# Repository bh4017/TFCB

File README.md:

# TFCB

# DESCRIPTION

A PIC 18F87J50 platform consisting of a baseboard which provides a means to easily design interface 'hats' for adding functionality.  

The baseboard includes all the basic components necessary to run an 18F87J50 Microcontroller, plus some communications ports (USB, RS232, SPI) and on-board power supplies.

The baseboard breaks out the 18F87J50 pins to 2.54mm IO which allows hats to be easily created by professional and amateur electronics users.  It is possible to build hats from stripboard or custom PCBs.  The 18F87J50 is extremely well equipped and even includes on-chip USB2.0, so USB based PIC projects can be created and prototyped very easily.

Some hats created by the author for various applications will be included under the /hats directory.

# LICENSE

This documentation describes Open Hardware and is licensed under the CERN Open Hardware Licence v1.2. You may redistribute and modify this documentation under the terms of the CERN OHL v1.2 (http://ohwr.org/cernohl). This documentation is distributed WITHOUT ANY EXPRESS OR IMPLIED WARRANTY, INCLUDING OF MERCHANTABILITY, SATISFACTORY QUALITY AND FITNESS FOR A PARTICULAR PURPOSE.  Please see the CERN OHL v1.2 for applicable conditions.

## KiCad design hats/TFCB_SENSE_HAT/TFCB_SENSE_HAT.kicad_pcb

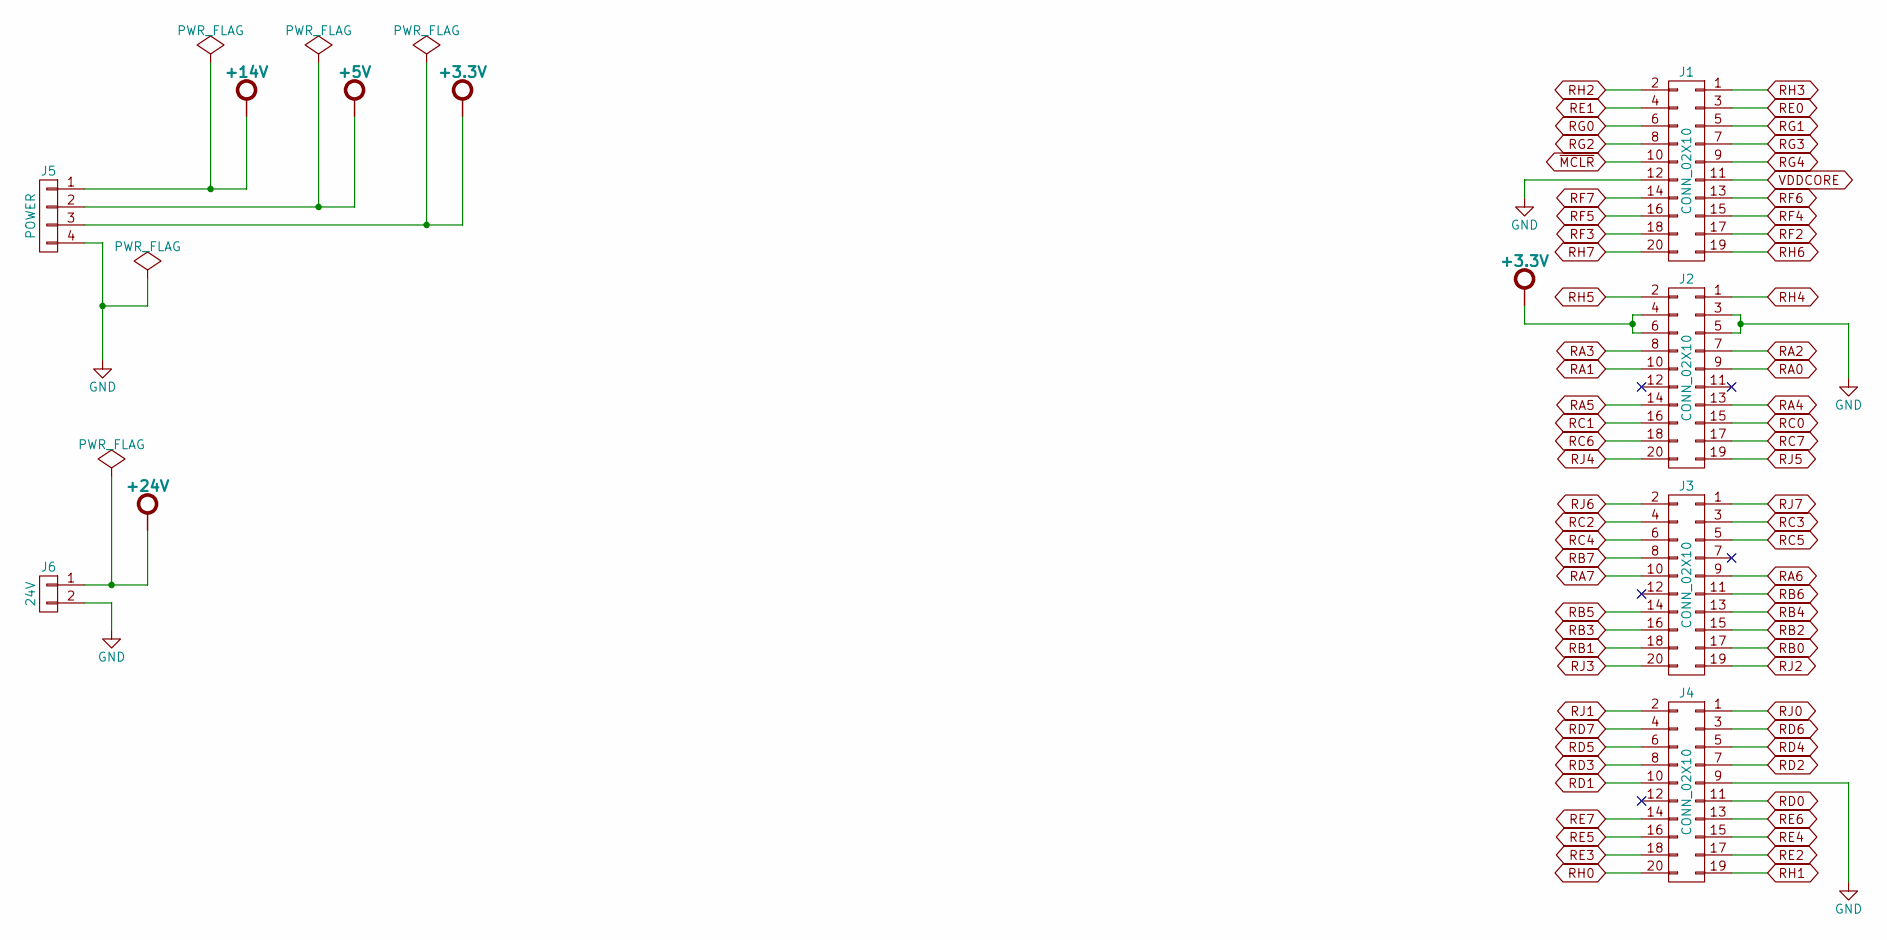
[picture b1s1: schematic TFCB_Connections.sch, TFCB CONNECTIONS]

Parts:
J1, J2, J3, J4: CONN_02X10; RCPT-2row-2.54mm-20way
J5: POWER; Weidmuller-SL-5.08-Vertical-4Pole
J6: 24V; Weidmuller-SL-5.08-Vertical-2Pole

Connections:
+3.3V: J2.4, J2.6, J5.3
+5V: J5.2
+14V: J5.1
+24V: J6.1
GND: J1.12, J2.3, J2.5, J4.9, J5.4, J6.2
RA0: J2.9
RA1: J2.10
RA2: J2.7
RA3: J2.8
RA4: J2.13
RA5: J2.14
RA6: J3.9
RA7: J3.10
RB0: J3.17
RB1: J3.18
RB2: J3.15
RB3: J3.16
RB4: J3.13
RB5: J3.14
RB6: J3.11
RB7: J3.8
RC0: J2.15
RC1: J2.16
RC2: J3.4
RC3: J3.3
RC4: J3.6
RC5: J3.5
RC6: J2.18
RC7: J2.17
RD0: J4.11
RD1: J4.10
RD2: J4.7
RD3: J4.8
RD4: J4.5
RD5: J4.6
RD6: J4.3
RD7: J4.4
RE0: J1.3
RE1: J1.4
RE2: J4.17
RE3: J4.18
RE4: J4.15
RE5: J4.16
RE6: J4.13
RE7: J4.14
RF2: J1.17
RF3: J1.18
RF4: J1.15
RF5: J1.16
RF6: J1.13
RF7: J1.14
RG0: J1.6
RG1: J1.5
RG2: J1.8
RG3: J1.7
RG4: J1.9
RH0: J4.20
RH1: J4.19
RH2: J1.2
RH3: J1.1
RH4: J2.1
RH5: J2.2
RH6: J1.19
RH7: J1.20
RJ0: J4.1
RJ1: J4.2
RJ2: J3.19
RJ3: J3.20
RJ4: J2.20
RJ5: J2.19
RJ6: J3.2
RJ7: J3.1
VDDCORE: J1.11
~MCLR: J1.10

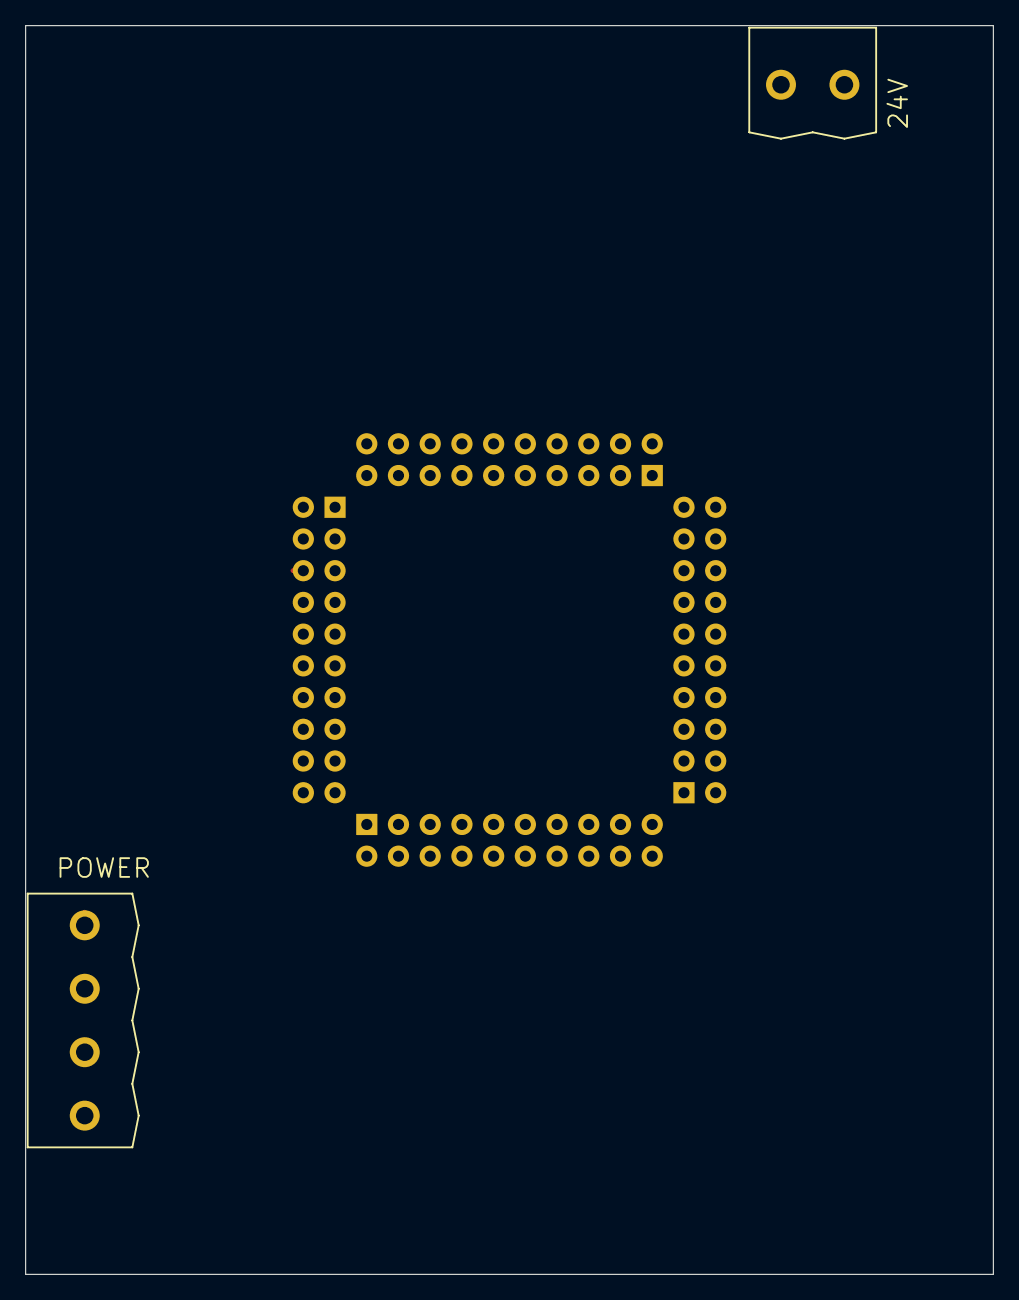
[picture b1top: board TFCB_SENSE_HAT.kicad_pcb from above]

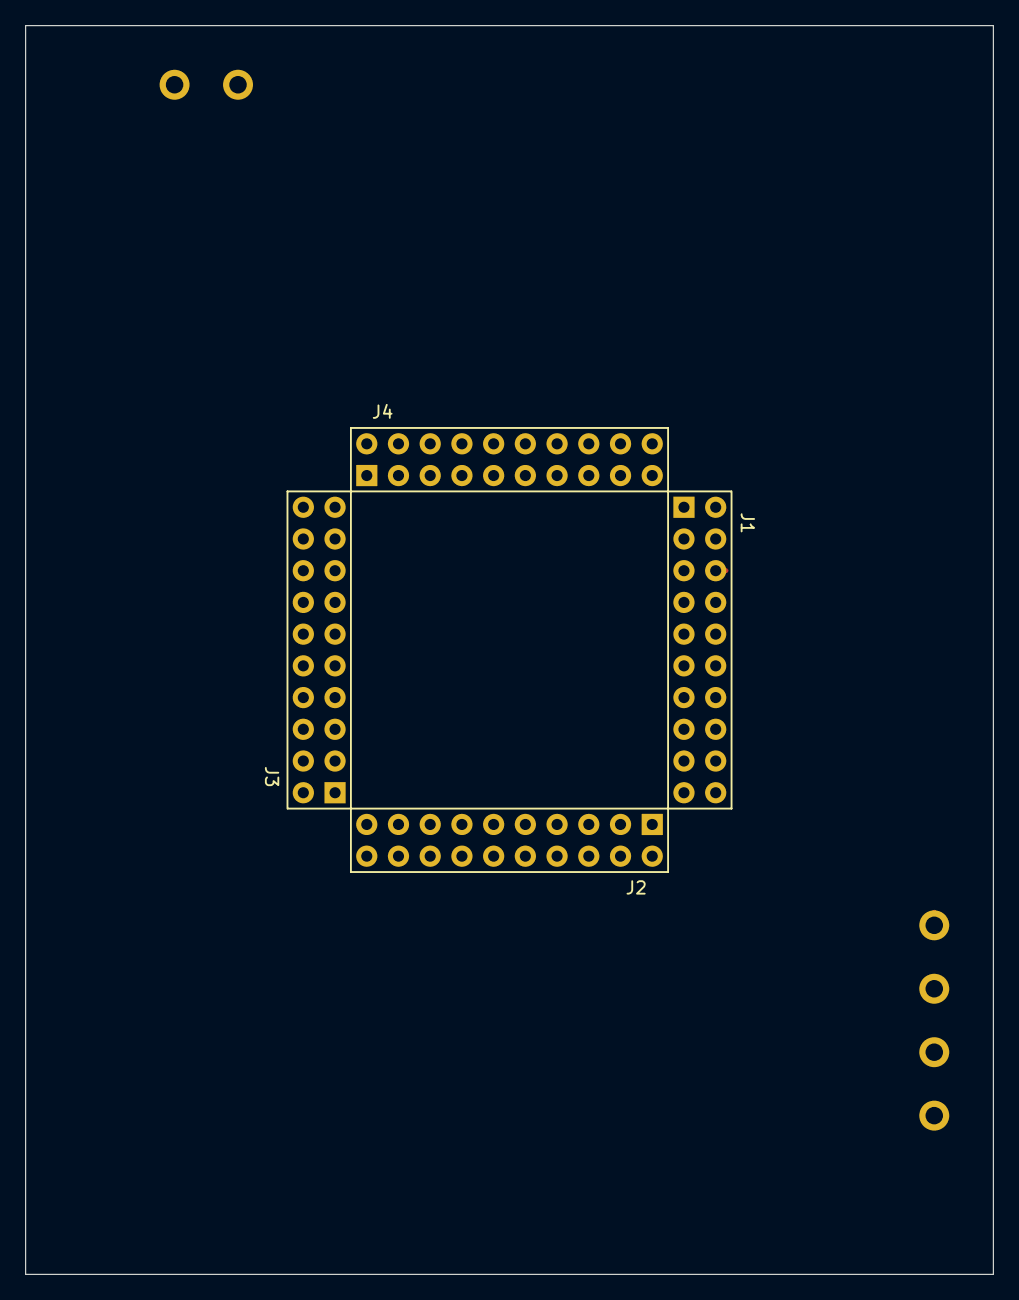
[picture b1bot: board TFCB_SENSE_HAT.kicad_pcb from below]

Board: 2 copper layers, 77.5 x 100.0 mm, 6 parts (4 on the bottom side), 2 nets.

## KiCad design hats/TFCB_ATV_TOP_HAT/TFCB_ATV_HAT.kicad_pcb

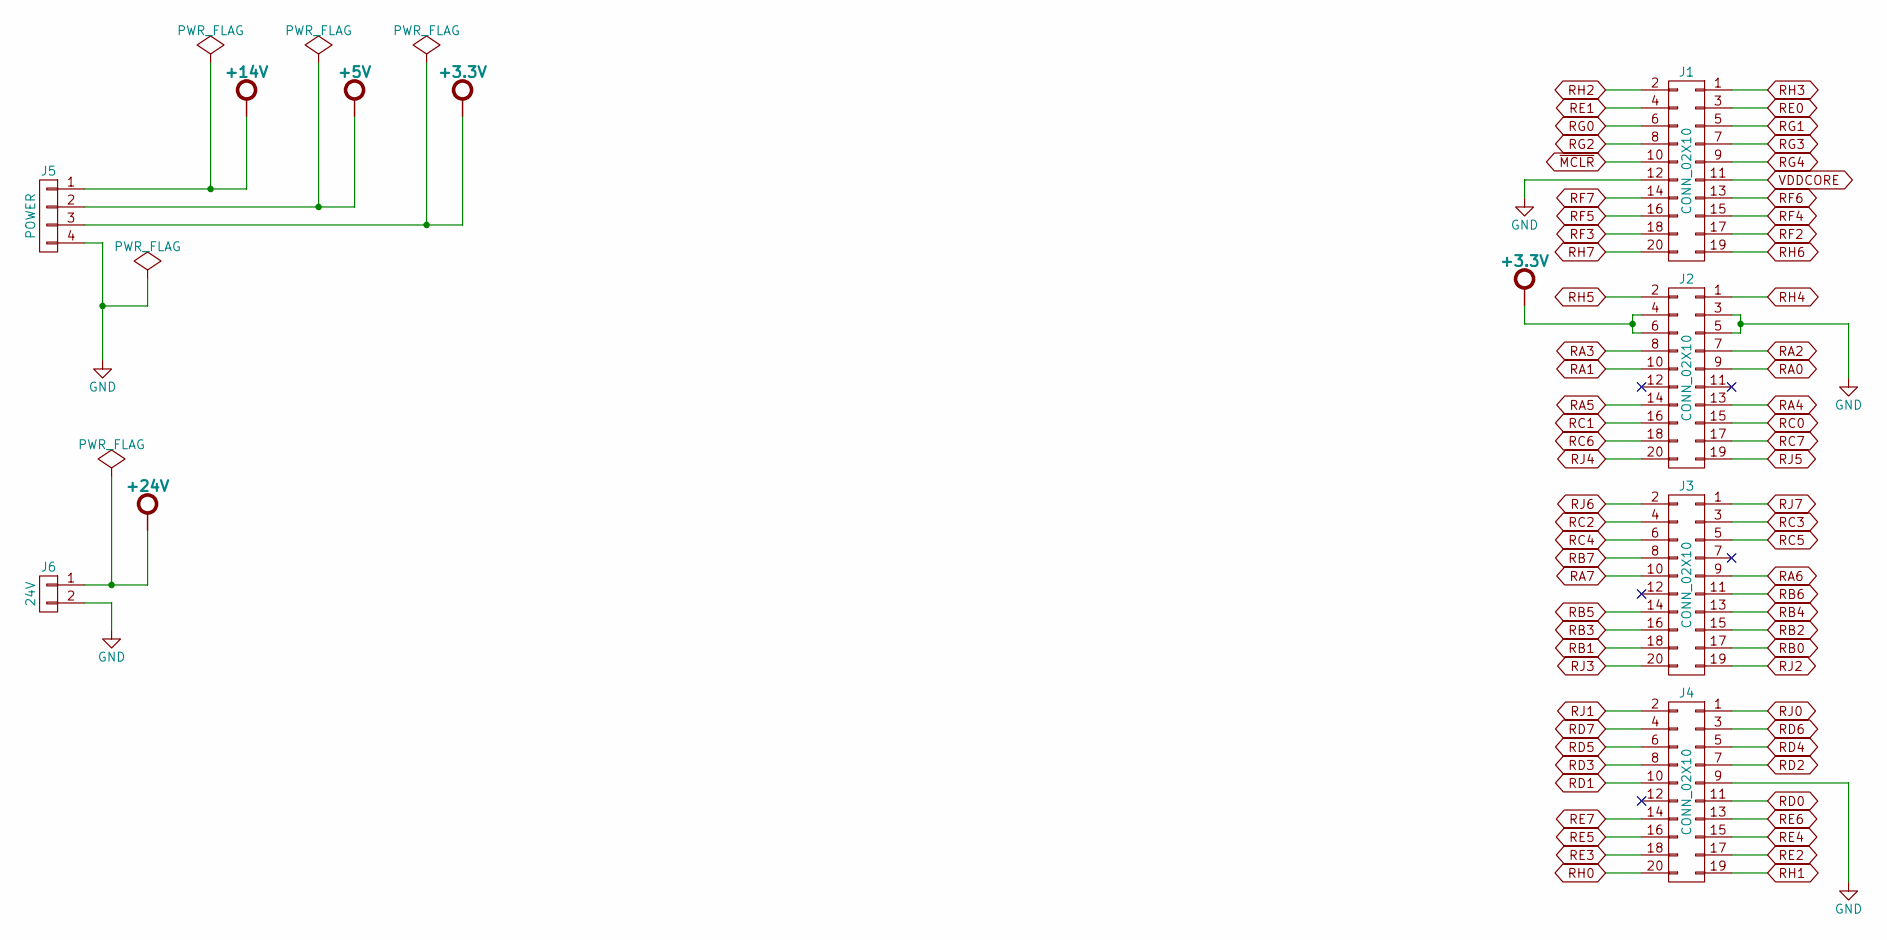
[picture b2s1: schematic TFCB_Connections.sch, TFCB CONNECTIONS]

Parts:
J1, J2, J3, J4: CONN_02X10; RCPT-2row-2.54mm-20way
J5: POWER; Weidmuller-SL-5.08-Vertical-4Pole
J6: 24V; Weidmuller-SL-5.08-Vertical-2Pole

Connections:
+3.3V: J2.4, J2.6, J5.3; also elsewhere on the board
+5V: J5.2; also elsewhere on the board
+14V: J5.1; also elsewhere on the board
+24V: J6.1; also elsewhere on the board
GND: J1.12, J2.3, J2.5, J4.9, J5.4, J6.2; also elsewhere on the board
RA0: J2.9; also elsewhere on the board
RA1: J2.10; also elsewhere on the board
RA2: J2.7
RA3: J2.8
RA4: J2.13; also elsewhere on the board
RA5: J2.14
RA6: J3.9
RA7: J3.10
RB0: J3.17
RB1: J3.18
RB2: J3.15
RB3: J3.16
RB4: J3.13
RB5: J3.14
RB6: J3.11
RB7: J3.8
RC0: J2.15
RC1: J2.16
RC2: J3.4; also elsewhere on the board
RC3: J3.3
RC4: J3.6
RC5: J3.5
RC6: J2.18
RC7: J2.17
RD0: J4.11
RD1: J4.10
RD2: J4.7
RD3: J4.8
RD4: J4.5
RD5: J4.6
RD6: J4.3
RD7: J4.4
RE0: J1.3
RE1: J1.4
RE2: J4.17
RE3: J4.18
RE4: J4.15
RE5: J4.16
RE6: J4.13; also elsewhere on the board
RE7: J4.14; also elsewhere on the board
RF2: J1.17; also elsewhere on the board
RF3: J1.18
RF4: J1.15
RF5: J1.16
RF6: J1.13
RF7: J1.14
RG0: J1.6; also elsewhere on the board
RG1: J1.5
RG2: J1.8
RG3: J1.7; also elsewhere on the board
RG4: J1.9; also elsewhere on the board
RH0: J4.20; also elsewhere on the board
RH1: J4.19
RH2: J1.2
RH3: J1.1
RH4: J2.1; also elsewhere on the board
RH5: J2.2; also elsewhere on the board
RJ0: J4.1
RJ1: J4.2
RJ2: J3.19
RJ3: J3.20; also elsewhere on the board
RJ4: J2.20
RJ5: J2.19
RJ6: J3.2; also elsewhere on the board
RJ7: J3.1; also elsewhere on the board
VDDCORE: J1.11
~MCLR: J1.10

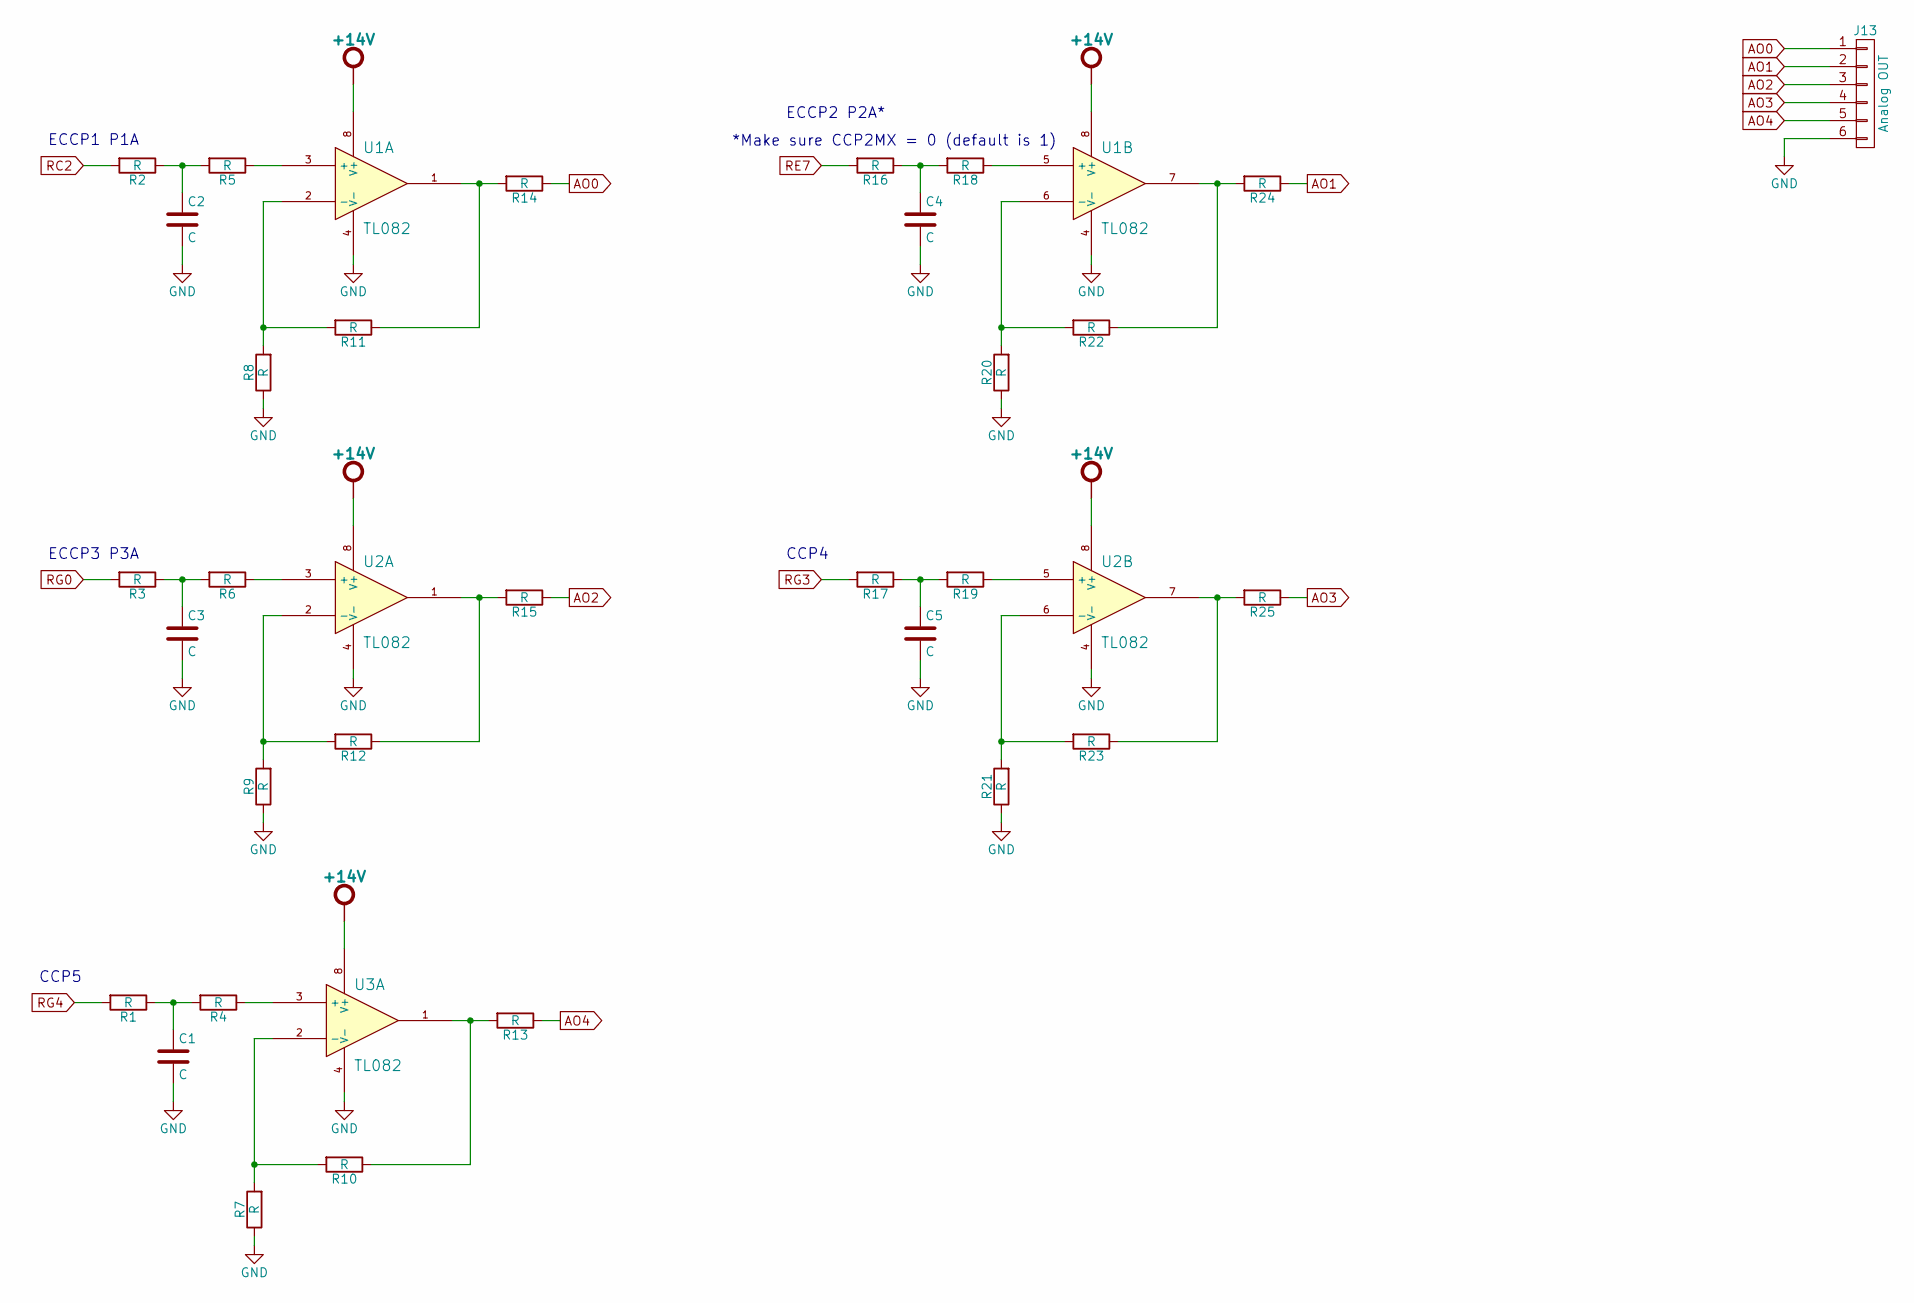
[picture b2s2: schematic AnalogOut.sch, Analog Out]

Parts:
C1, C2, C3, C4, C5: C; C_0805_HandSoldering
J13: Analog OUT; Weidmuller-SL-5.08-Vertical-6Pole
R1, R2, R3, R4, R5, R6, R7, R8, R9, R10, R11, R12, R13, R14, R15, R16, R17, R18, R19, R20, R21, R22, R23, R24, R25: R; R_0805_HandSoldering
U1, U2, U3: TL082; SOIC-8_3.9x4.9mm_Pitch1.27mm

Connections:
+14V: U1.8 (V+), U2.8 (V+), U3.8 (V+); also elsewhere on the board
AO0: J13.1, R14.1
AO1: J13.2, R24.1
AO2: J13.3, R15.1
AO3: J13.4, R25.1
AO4: J13.5, R13.1
GND: C1.2, C2.2, C3.2, C4.2, C5.2, J13.6, R7.1, R8.1, R9.1, R20.1, R21.1, U1.4 (V-), U2.4 (V-), U3.4 (V-); also elsewhere on the board
unnamed: C1.1, R1.1, R4.2
unnamed: C2.1, R2.1, R5.2
unnamed: C3.1, R3.1, R6.2
unnamed: C4.1, R16.1, R18.2
unnamed: C5.1, R17.1, R19.2
unnamed: R4.1, U3.3 (+)
unnamed: R5.1, U1.3 (+)
unnamed: R6.1, U2.3 (+)
unnamed: R10.1, R13.2, U3.1
unnamed: R7.2, R10.2, U3.2 (-)
unnamed: R11.1, R14.2, U1.1
unnamed: R8.2, R11.2, U1.2 (-)
unnamed: R12.1, R15.2, U2.1
unnamed: R9.2, R12.2, U2.2 (-)
unnamed: R18.1, U1.5 (+)
unnamed: R19.1, U2.5 (+)
unnamed: R20.2, R22.2, U1.6 (-)
unnamed: R21.2, R23.2, U2.6 (-)
unnamed: R22.1, R24.2, U1.7
unnamed: R23.1, R25.2, U2.7
RC2: R2.2; also elsewhere on the board
RE7: R16.2; also elsewhere on the board
RG0: R3.2; also elsewhere on the board
RG3: R17.2; also elsewhere on the board
RG4: R1.2; also elsewhere on the board

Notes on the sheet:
ECCP1 P1A
ECCP3 P3A
ECCP2 P2A*
CCP5
CCP4
*Make sure CCP2MX = 0 (default is 1)

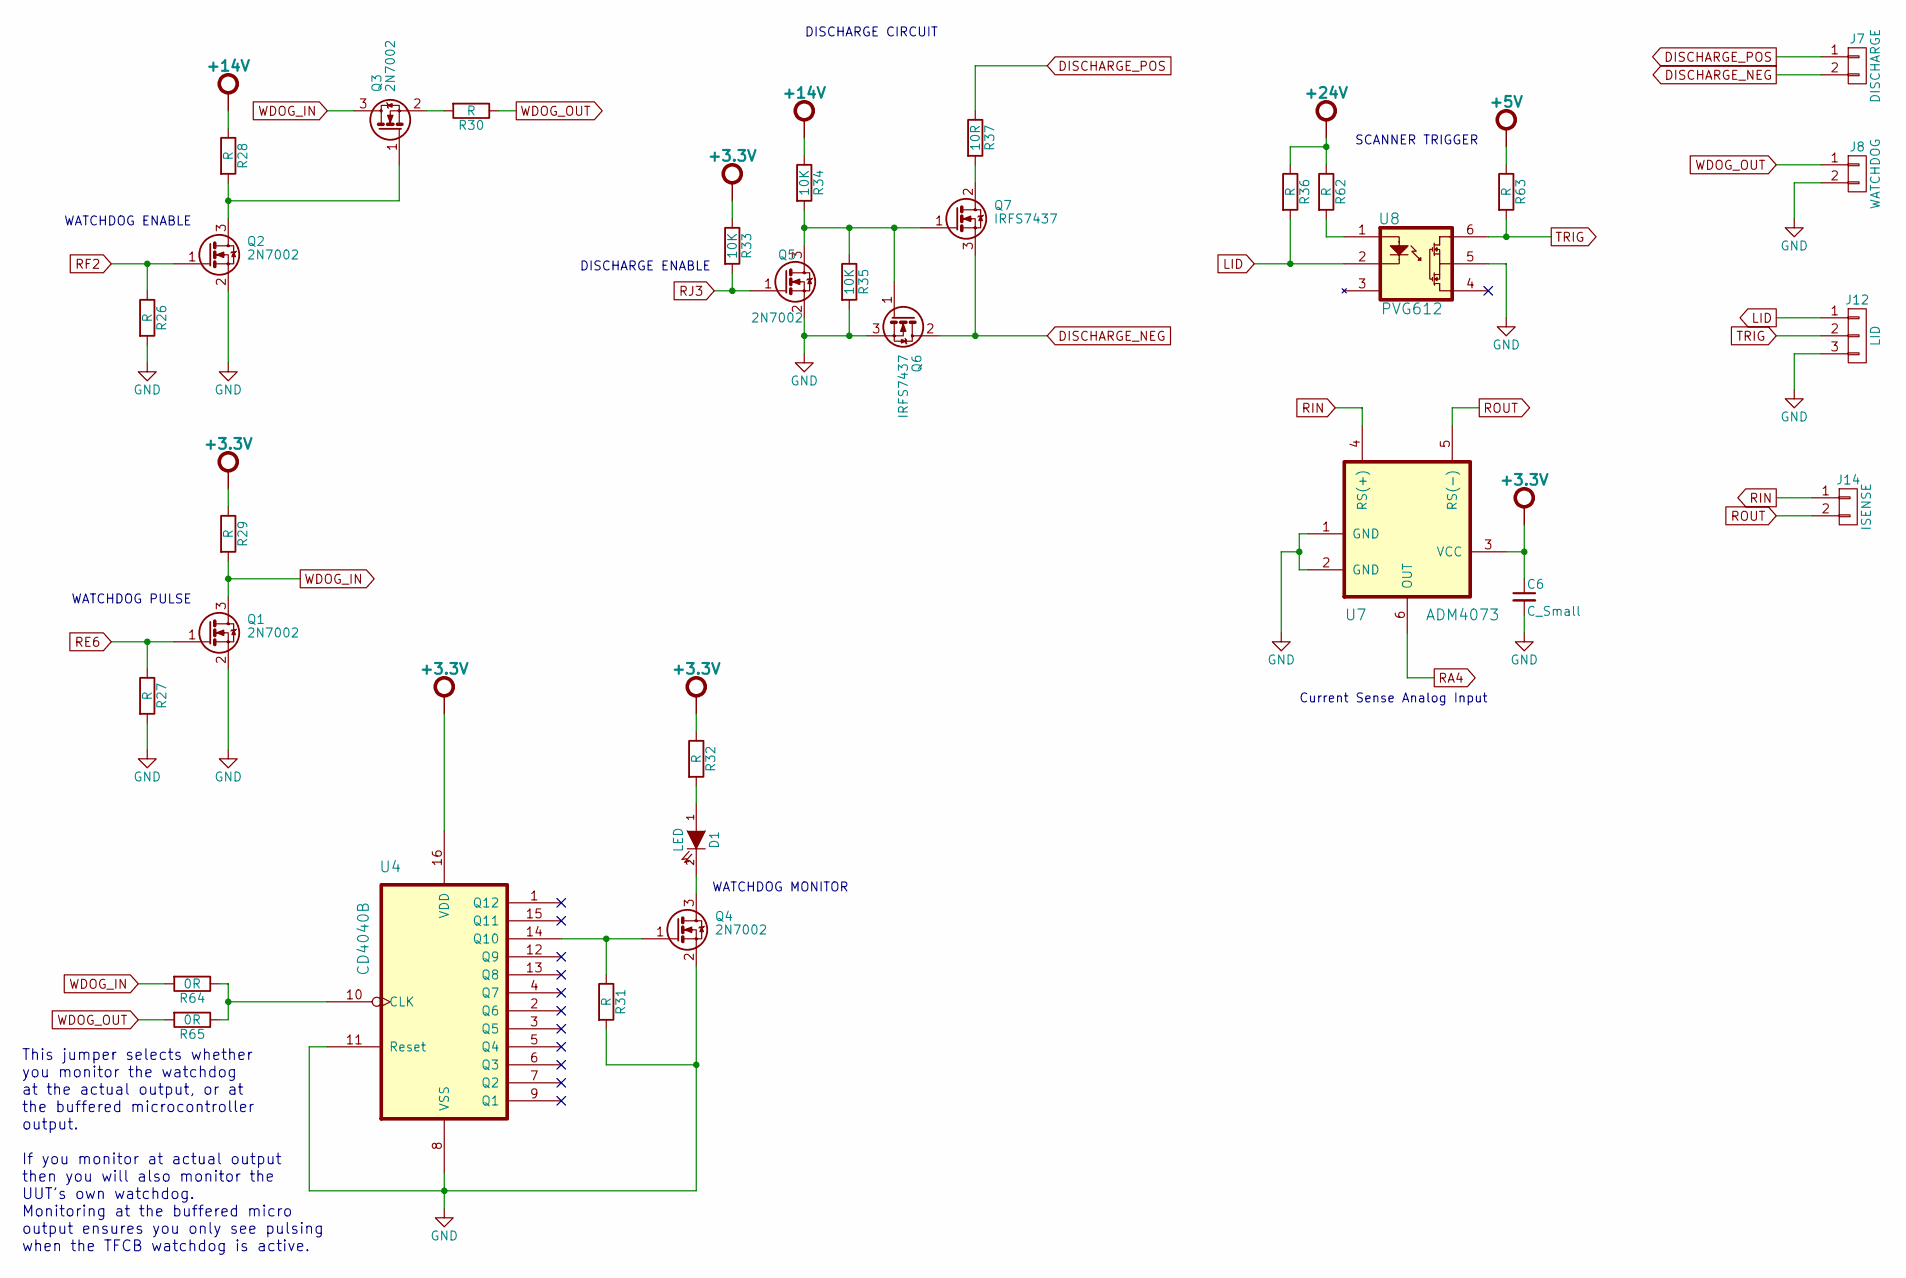
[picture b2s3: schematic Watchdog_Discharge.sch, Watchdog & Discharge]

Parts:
C6: C_Small; C_0805_HandSoldering
D1: LED; LED-1206
J7: DISCHARGE; Weidmuller-SL-5.08-Vertical-2Pole
J8: WATCHDOG; Weidmuller-SL-5.08-Vertical-2Pole
J12: LID; Weidmuller-SL-5.08-Vertical-3Pole
J14: ISENSE; Weidmuller-SL-5.08-Vertical-2Pole
Q1, Q2, Q3, Q4, Q5: 2N7002; SOT-23
Q6, Q7: IRFS7437; DPAK-2
R26, R27, R28, R29, R30, R31, R32, R36, R62, R63: R; R_0805_HandSoldering
R33, R34, R35: 10K; R_0805_HandSoldering
R37: 10R; PWR5322_SMD
R64, R65: 0R; R_0805_HandSoldering
U4: CD4040B; SOIC-16_3.9x9.9mm_Pitch1.27mm
U7: ADM4073; SC-70-6
U8: PVG612; IR-MicroSSRelay-6Pin-SMT

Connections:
+3.3V: C6.1, R29.1, R32.1, R33.1, U4.16 (VDD), U7.3 (VCC); also elsewhere on the board
+5V: R63.1; also elsewhere on the board
+14V: R28.1, R34.1; also elsewhere on the board
+24V: R36.1, R62.1; also elsewhere on the board
DISCHARGE_NEG: J7.2, Q6.2 (D), Q7.3 (S)
DISCHARGE_POS: J7.1, R37.1
GND: C6.2, J8.2, J12.3, Q1.2 (S), Q2.2 (S), Q4.2 (S), Q5.2 (S), Q6.3 (S), R26.2, R27.2, R31.2, R35.2, U4.8 (VSS), U4.11 (Reset), U7.1 (GND), U7.2 (GND), U8.5; also elsewhere on the board
LID: J12.1, R36.2, U8.2
unnamed: D1.1 (A), R32.2
unnamed: D1.2 (K), Q4.3 (D)
unnamed: Q2.3 (D), Q3.1 (G), R28.2
unnamed: Q3.2 (S), R30.2
unnamed: Q4.1 (G), R31.1, U4.14 (Q10)
unnamed: Q5.3 (D), Q6.1 (G), Q7.1 (G), R34.2, R35.1
unnamed: Q7.2 (D), R37.2
unnamed: R62.2, U8.1
unnamed: R64.1, R65.1, U4.10 (CLK)
RA4: U7.6 (OUT); also elsewhere on the board
RE6: Q1.1 (G), R27.1; also elsewhere on the board
RF2: Q2.1 (G), R26.1; also elsewhere on the board
RIN: J14.1, U7.4 (RS(+))
RJ3: Q5.1 (G), R33.2; also elsewhere on the board
ROUT: J14.2, U7.5 (RS(-))
TRIG: J12.2, R63.2, U8.6
WDOG_IN: Q1.3 (D), Q3.3 (D), R29.2, R64.2
WDOG_OUT: J8.1, R30.1, R65.2

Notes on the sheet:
WATCHDOG ENABLE
WATCHDOG PULSE
WATCHDOG MONITOR
DISCHARGE CIRCUIT
DISCHARGE ENABLE
This jumper selects whether you monitor the watchdog at the actual output, or at the buffered microcontroller output. If you monitor at actual output then you will also monitor the UUT's own watchdog. Monitoring at the buffered micro output ensures you only see pulsing when the TFCB watchdog is act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
SCANNER TRIGGER
Current Sense Analog Input

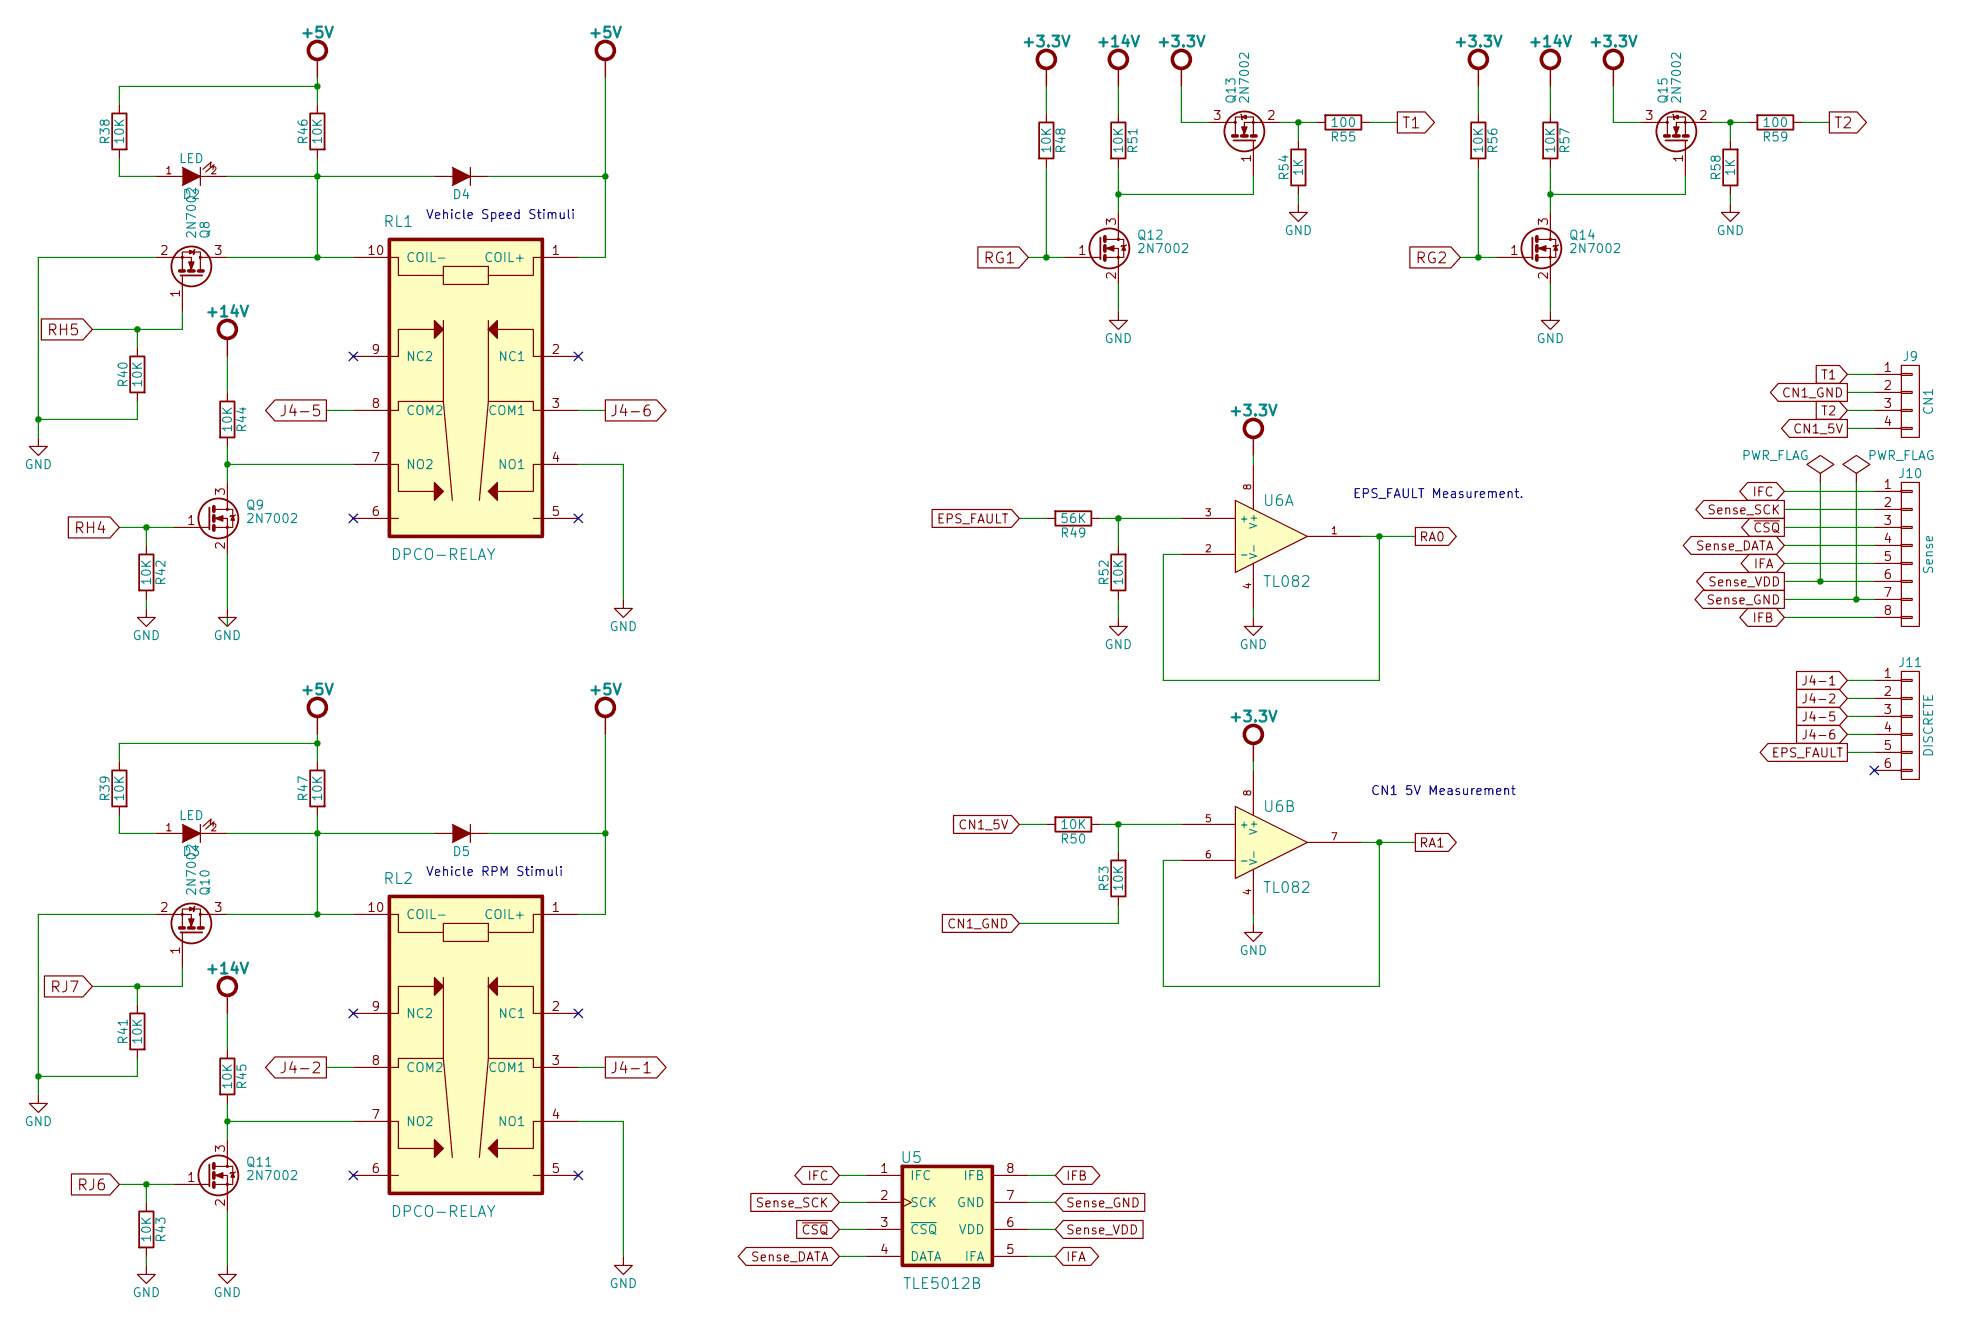
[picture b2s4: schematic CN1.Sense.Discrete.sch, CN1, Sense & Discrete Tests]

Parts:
D2, D3: LED; LED-1206
D4, D5: D-BJH
J9: CN1; Weidmuller-SL-5.08-Vertical-4Pole
J10: Sense; Weidmuller-SL-5.08-Vertical-8Pole
J11: DISCRETE; Weidmuller-SL-5.08-Vertical-6Pole
Q8, Q9, Q10, Q11, Q12, Q13, Q14, Q15: 2N7002; SOT-23
R38, R39, R40, R41, R42, R43, R44, R45, R46, R47, R48, R50, R51, R52, R53, R56, R57: 10K; R_0805_HandSoldering
R49: 56K; R_0805_HandSoldering
R54, R58: 1K; R_0805_HandSoldering
R55, R59: 100; R_0805_HandSoldering
RL1, RL2: DPCO-RELAY; EB2-5NU
U5: TLE5012B; SOIC-8_3.9x4.9mm_Pitch1.27mm
U6: TL082; SOIC-8_3.9x4.9mm_Pitch1.27mm

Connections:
+3.3V: Q13.3 (D), Q15.3 (D), R48.1, R56.1, U6.8 (V+); also elsewhere on the board
+5V: D4.K, D5.K, R38.1, R39.1, R46.1, R47.1, RL1.1 (COIL+), RL2.1 (COIL+); also elsewhere on the board
+14V: R44.1, R45.1, R51.1, R57.1; also elsewhere on the board
CN1_5V: J9.4, R50.2
CN1_GND: J9.2, R53.1
EPS_FAULT: J11.5, R49.2
GND: Q8.2 (S), Q9.2 (S), Q10.2 (S), Q11.2 (S), Q12.2 (S), Q14.2 (S), R40.2, R41.2, R42.2, R43.2, R52.1, R54.1, R58.1, RL1.4 (NO1), RL2.4 (NO1), U6.4 (V-); also elsewhere on the board
IFA: J10.5, U5.5 (IFA)
IFB: J10.8, U5.8 (IFB)
IFC: J10.1, U5.1 (IFC)
J4-1: J11.1, RL2.3 (COM1)
J4-2: J11.2, RL2.8 (COM2)
J4-5: J11.3, RL1.8 (COM2)
J4-6: J11.4, RL1.3 (COM1)
unnamed: D2.1 (A), R38.2
unnamed: D2.2 (K), D4.A, Q8.3 (D), R46.2, RL1.10 (COIL-)
unnamed: D3.1 (A), R39.2
unnamed: D3.2 (K), D5.A, Q10.3 (D), R47.2, RL2.10 (COIL-)
unnamed: Q9.3 (D), R44.2, RL1.7 (NO2)
unnamed: Q11.3 (D), R45.2, RL2.7 (NO2)
unnamed: Q12.3 (D), Q13.1 (G), R51.2
unnamed: Q13.2 (S), R54.2, R55.2
unnamed: Q14.3 (D), Q15.1 (G), R57.2
unnamed: Q15.2 (S), R58.2, R59.2
unnamed: R49.1, R52.2, U6.3 (+)
unnamed: R50.1, R53.2, U6.5 (+)
RA0: U6.1, U6.2 (-); also elsewhere on the board
RA1: U6.6 (-), U6.7; also elsewhere on the board
RH4: Q9.1 (G), R42.1; also elsewhere on the board
RH5: Q8.1 (G), R40.1; also elsewhere on the board
RJ6: Q11.1 (G), R43.1; also elsewhere on the board
RJ7: Q10.1 (G), R41.1; also elsewhere on the board
Sense_DATA: J10.4, U5.4 (DATA)
Sense_GND: J10.7, U5.7 (GND)
Sense_SCK: J10.2, U5.2 (SCK)
Sense_VDD: J10.6, U5.6 (VDD)
T1: J9.1, R55.1
T2: J9.3, R59.1
~CSQ: J10.3, U5.3 (~CSQ)

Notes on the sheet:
Vehicle Speed Stimuli
EPS_FAULT Measurement.
CN1 5V Measurement
Vehicle RPM Stimuli

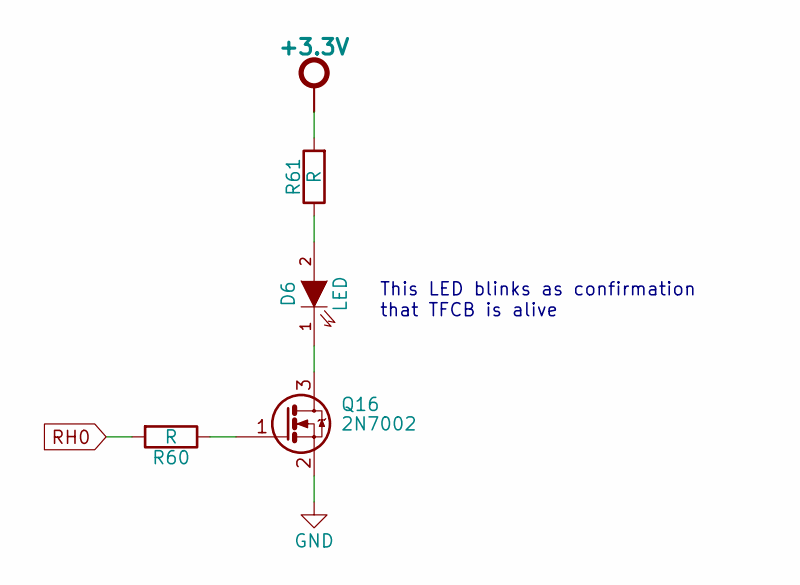
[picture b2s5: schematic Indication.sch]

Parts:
D6: LED; LED-1206
Q16: 2N7002; SOT-23
R60, R61: R; R_0805_HandSoldering

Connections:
+3.3V: R61.2; also elsewhere on the board
GND: Q16.2 (S); also elsewhere on the board
unnamed: D6.1 (K), Q16.3 (D)
unnamed: D6.2 (A), R61.1
unnamed: Q16.1 (G), R60.1
RH0: R60.2; also elsewhere on the board

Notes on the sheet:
This LED blinks as confirmation that TFCB is alive

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
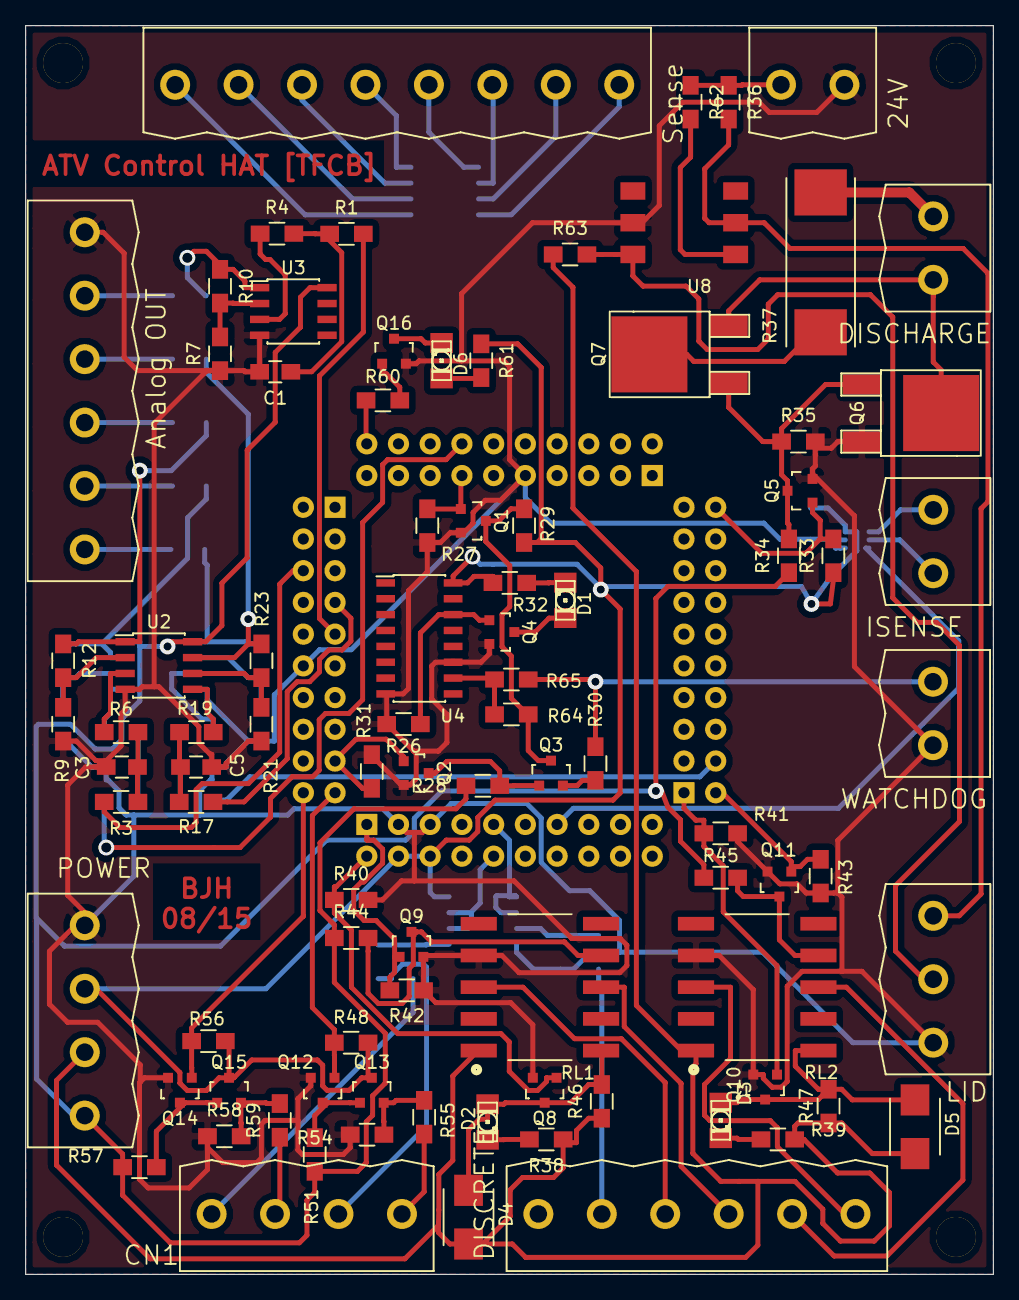
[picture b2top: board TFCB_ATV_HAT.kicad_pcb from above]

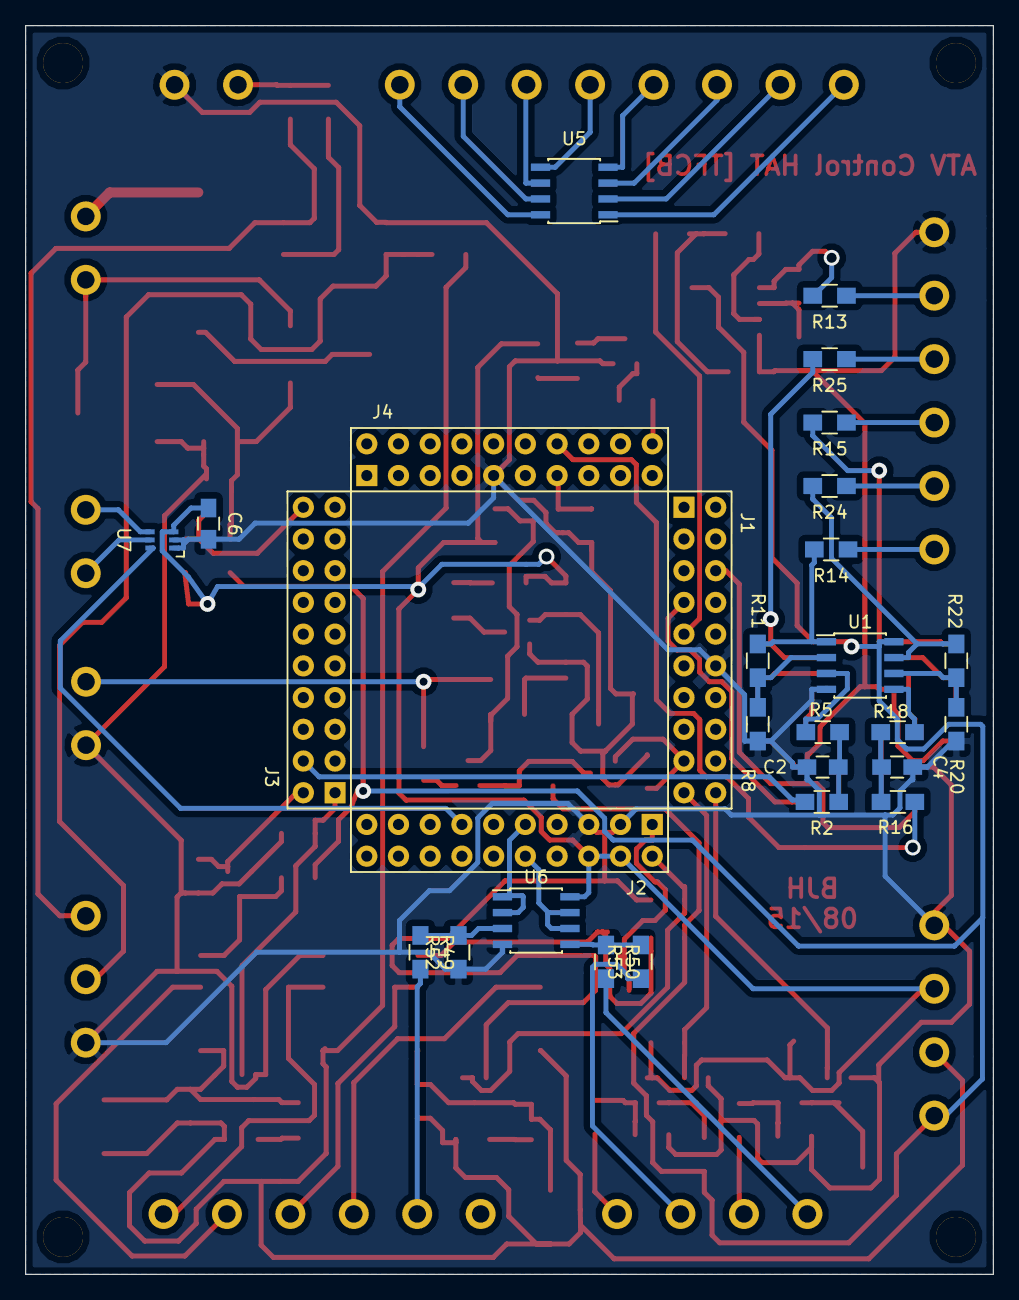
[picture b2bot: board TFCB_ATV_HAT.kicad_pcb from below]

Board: 2 copper layers, 77.5 x 100.0 mm, 121 parts (28 on the bottom side), 97 nets.

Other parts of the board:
Mount1, Mount2, Mount3, Mount4: MountingHole_3-2mm
